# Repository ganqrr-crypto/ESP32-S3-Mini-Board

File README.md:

This is my custom ESP32 S3 mini project. I am making this project to replace my currently borrowed from a friend arduino uno.. yea.
All things aside this is a ESP32 board whit a mini chip and i really wanted to make one to see this much packed power into so much small thing. i havent used all gpios cause i was worried about some routing if you look in the schematics you will see
and i loved making it.
it has a LED on the 3.3 too so when you plug in it will light up. It uses USB C and has a picture of my cat on the back.

BOM:
| Part | Quantity | Cost USD | Vendor | Link |
|---|---:|---:|---|---|
| PCB | 5 | $3.60 | AIVON | [Link](https://www.aivon.com/) |
| ESP32-S3-MINI | 1 | $5.01 | TME | [Link](https://www.tme.eu/it/details/esp32s3-mini-1-8/moduli-iot-wifi-bluetooth/espressif/esp32-s3-mini-1-n8/) |
| 100nF Capacitor | 10 | $0.32 | TME | [Link](https://www.tme.eu/it/details/0603b104k500ct/condensatori-mlcc-smd/walsin/) |
| 10uF capacitor | 5 | $1.23 | TME | [Link](https://www.tme.eu/it/details/c0603c106m9pac/condensatori-mlcc-smd/kemet/c0603c106m9pactu/) |
| 603 led | 1 | $0.54 | TME | [Link](https://www.tme.eu/it/details/sm0603gcl/diodi-led-smd-colorati/bivar/) |
| USB C | 1 | $0.73 | TME | [Link](https://www.tme.eu/it/details/usb4105-gf-a/connettori-usb-e-ieee-1394/gct/) |
| Headers | 10 | $1.67 | TME | [Link](https://www.tme.eu/it/details/zl201-16g/connettore-dell-intestazione-di-pin/connfly/ds1021-1-16sf11/) |
| 5k1 Resistor | 10 | $0.16 | TME | [Link](https://www.tme.eu/it/details/ac0603fr-075k1l/resistori-smd/yageo/) |
| 10k | 10 | $0.2 | TME | [Link](https://www.tme.eu/it/details/rc0603fr-0710k/resistori-smd/yageo/rc0603fr-0710kl/) |
| 1k resistor | 10 | $0.15 | TME | [Link](https://www.tme.eu/it/details/rc0603fr-071k/resistori-smd/yageo/rc0603fr-071kl/) |
| Buttons | 2 | $1.03 | TME | [Link](https://www.tme.eu/it/details/pts810sjm250smtrlf/microinterruttori-tact/c-k/pts810sjm250smtr-lfs/) |
| USBLC6-2SC6 | 1 | $0.45 | TME | [Link](https://www.tme.eu/it/details/usblc6-2sc6/diodi-di-protezione-reti/stmicroelectronics/) |
| TLV75733PDBVR | 1 | $0.25 | TME | [Link](https://www.tme.eu/it/details/tlv75733pdbvr/stabilizzatori-di-tens-non-regol-ldo/texas-instruments/) |

TOTAL WITH TAX AND SHIPPING: $44.87

PCB 

SCHEMATICS

BOARD

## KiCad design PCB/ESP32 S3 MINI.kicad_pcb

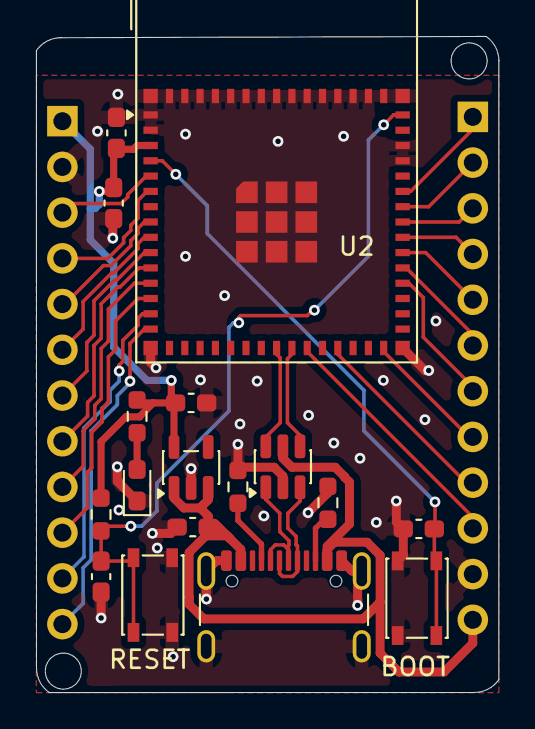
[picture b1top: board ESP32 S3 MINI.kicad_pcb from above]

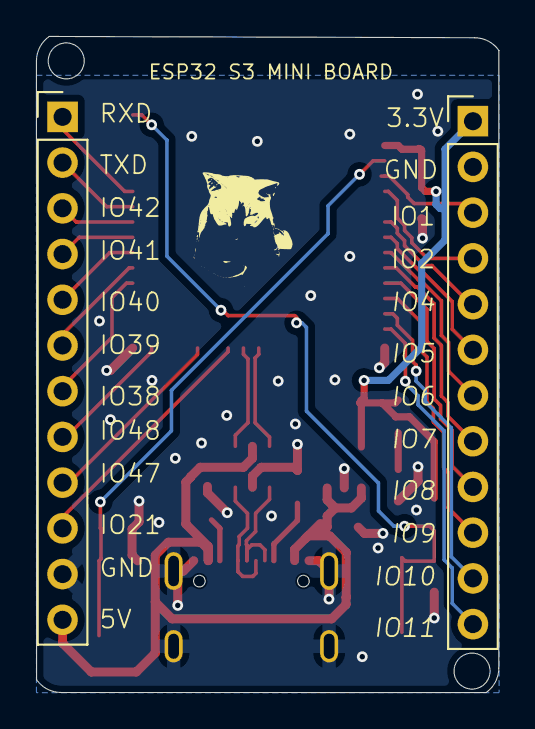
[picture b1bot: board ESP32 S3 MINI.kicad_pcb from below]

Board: 2 copper layers, 25.7 x 36.5 mm, 19 parts (2 on the bottom side), 32 nets.

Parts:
BOOT: BOOT; SW_SPST_PTS810
C1, C3, C4: 10uF; C_0603_1608Metric_Pad1.08x0.95mm_HandSolder
C2, C5, C6: 100nF; C_0603_1608Metric_Pad1.08x0.95mm_HandSolder
D1: LED; LED_0603_1608Metric_Pad1.05x0.95mm_HandSolder
J1: USB_C_Receptacle_USB2.0_16P; USB_C_Receptacle_GCT_USB4105-xx-A_16P_TopMnt_Horizontal
J2, J3: Conn_01x12_Pin; PinHeader_1x12_P2.54mm_Vertical
R1, R2: 5K1; R_0603_1608Metric_Pad0.98x0.95mm_HandSolder
R3: 10K; R_0603_1608Metric_Pad0.98x0.95mm_HandSolder
R4: 1k; R_0603_1608Metric_Pad0.98x0.95mm_HandSolder
RESET: RESET; SW_SPST_PTS810
U1: USBLC6-2SC6; SOT-23-6
U2: ESP32-S3-MINI-1; ESP32-S2-MINI-1
U3: TLV75733PDBV; SOT-23-5

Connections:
+3.3V: C1.2, C2.2, C4.2, J2.1, R3.1, R4.2, U2.3 (3V3), U3.5 (OUT)
/D+: U1.4 (I/O2), U2.24 (USB_D+)
/D-: U1.6 (I/O1), U2.23 (USB_D-)
/IO1: J2.3, U2.5 (IO1)
/IO2: J2.4, U2.6 (IO2)
/IO4: J2.5, U2.8 (IO4)
/IO5: J2.6, U2.9 (IO5)
/IO6: J2.7, U2.10 (IO6)
/IO7: J2.8, U2.11 (IO7)
/IO8: J2.9, U2.12 (IO8)
/IO9: J2.10, U2.13 (IO9)
/IO10: J2.11, U2.14 (IO10)
/IO11: J2.12, U2.15 (IO11)
/IO21: J3.10, U2.25 (IO21)
/IO38: J3.7, U2.34 (IO38)
/IO39: J3.6, U2.35 (IO39)
/IO40: J3.5, U2.36 (IO40)
/IO41: J3.4, U2.37 (IO41)
/IO42: J3.3, U2.38 (IO42)
/IO47: J3.9, U2.27 (IO47)
/IO48: J3.8, U2.30 (IO48)
/RAW D+: J1.A6 (D+), J1.B6 (D+), U1.3 (I/O2)
/RAW D-: J1.A7 (D-), J1.B7 (D-), U1.1 (I/O1)
/RXD: J3.1, U2.40 (RXD0)
/TXD: J3.2, U2.39 (TXD0)
GND: BOOT.1, C1.1, C2.1, C3.1, C4.1, C5.2, C6.1, D1.1 (K), J1.A1 (GND), J1.A12 (GND), J1.B1 (GND), J1.B12 (GND), J1.SH (SHIELD), J2.2, J3.11, R1.2, R2.2, RESET.1, U1.2 (GND), U2.1 (GND), U2.2 (GND), U2.42 (GND), U2.43 (GND), U2.46 (GND), U2.47 (GND), U2.48 (GND), U2.49 (GND), U2.50 (GND), U2.51 (GND), U2.52 (GND), U2.53 (GND), U2.54 (GND), U2.55 (GND), U2.56 (GND), U2.57 (GND), U2.58 (GND), U2.59 (GND), U2.60 (GND), U2.61 (GND), U2.62 (GND), U2.63 (GND), U2.64 (GND), U2.65 (GND), U3.2 (GND)
unnamed: D1.2 (A), R4.1
unnamed: J1.A5 (CC1), R1.1
unnamed: J1.B5 (CC2), R2.1
unnamed: C5.1, R3.2, RESET.2, U2.45 (EN)
unnamed: BOOT.2, C6.2, U2.4 (IO0)
VBUS: C3.2, J1.A4 (VBUS), J1.A9 (VBUS), J1.B4 (VBUS), J1.B9 (VBUS), J3.12, U1.5 (VBUS), U3.1 (IN), U3.3 (EN)
